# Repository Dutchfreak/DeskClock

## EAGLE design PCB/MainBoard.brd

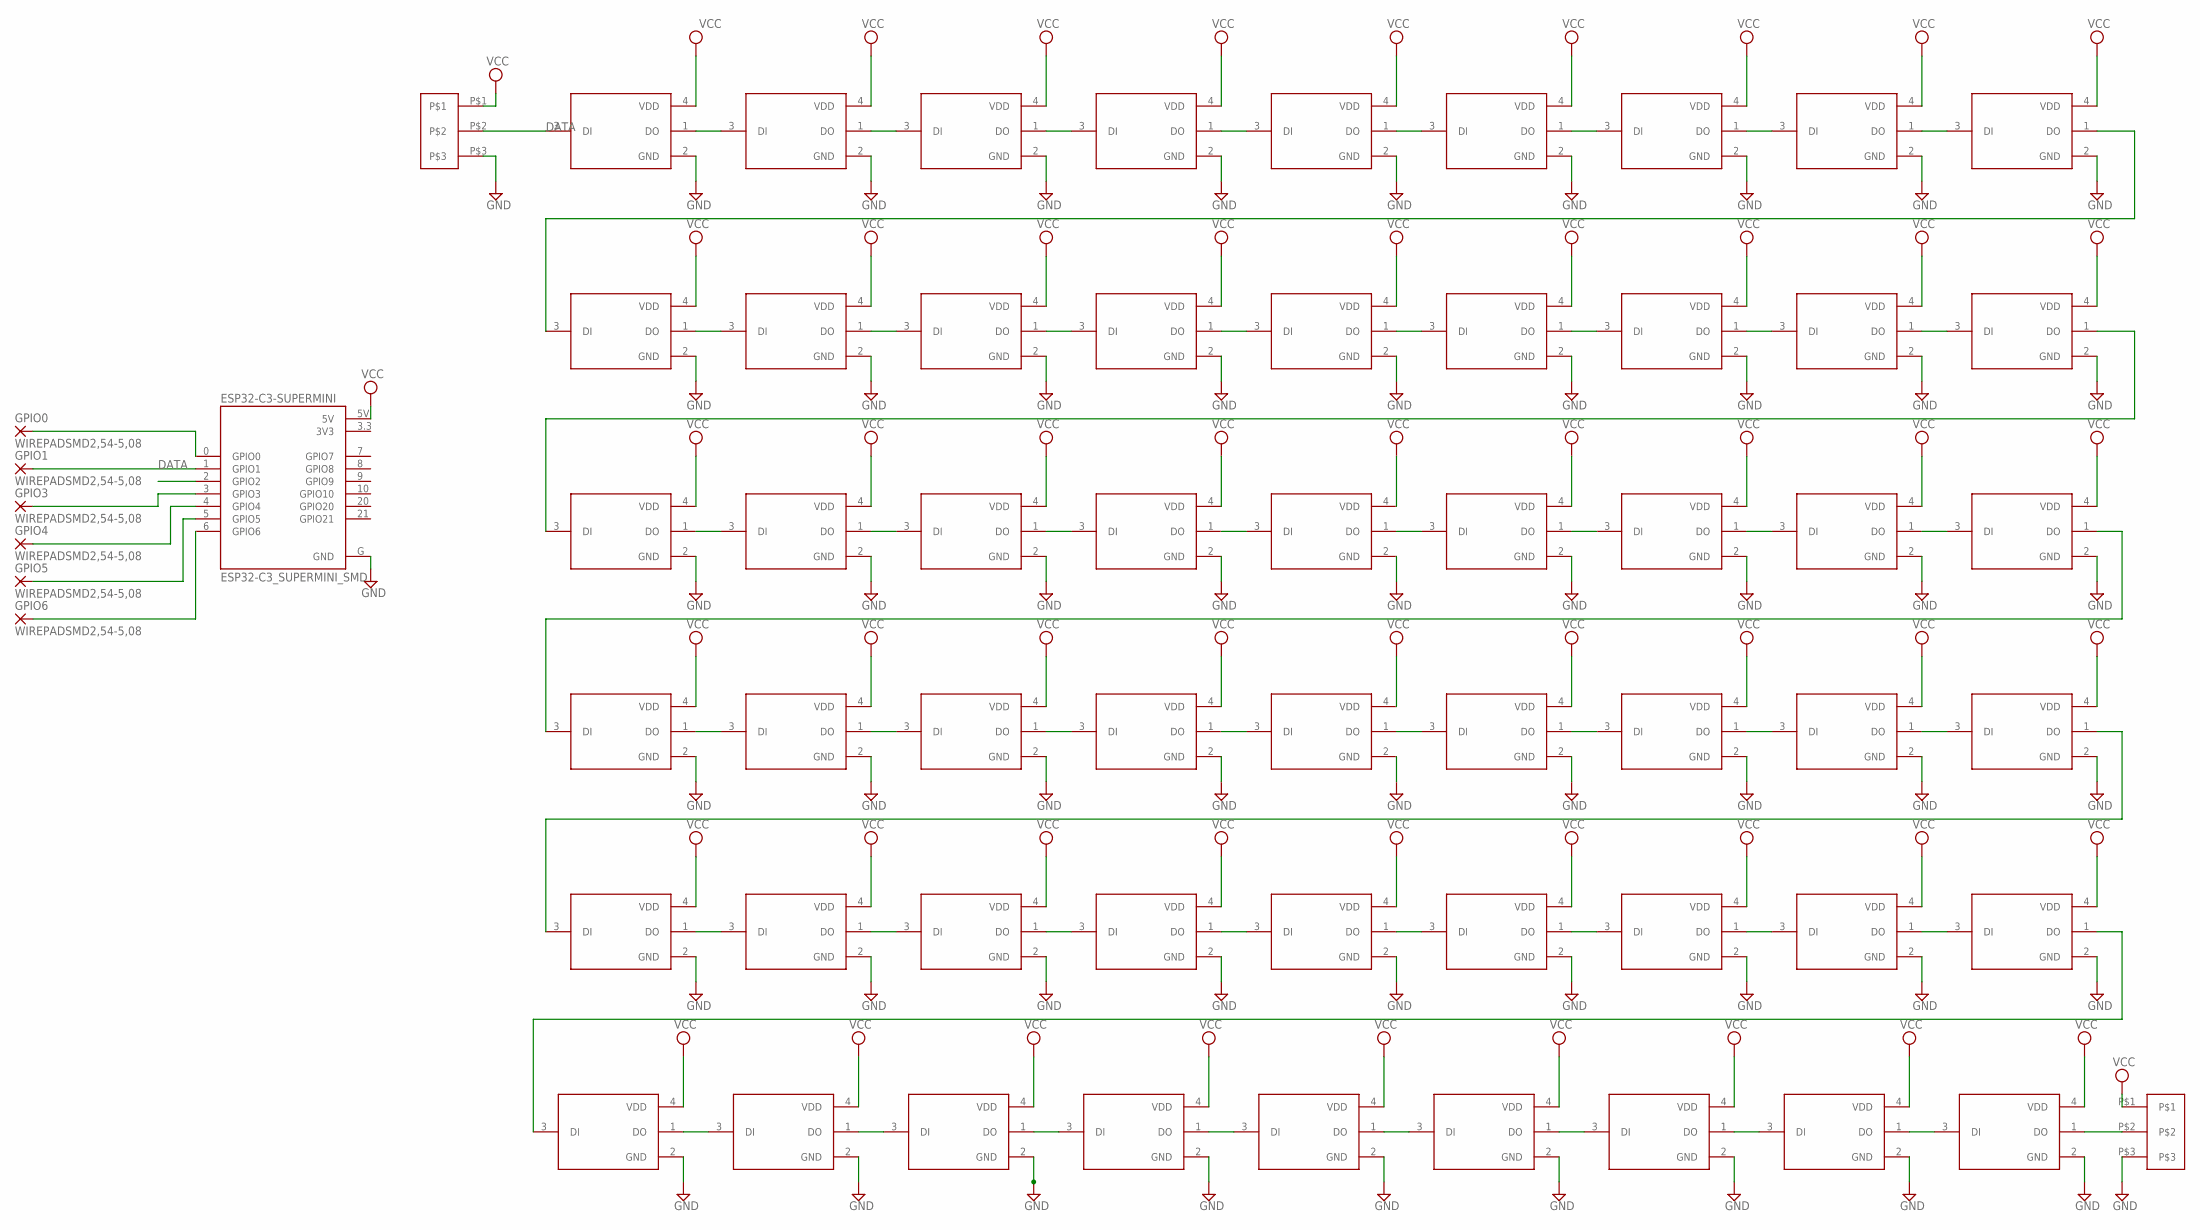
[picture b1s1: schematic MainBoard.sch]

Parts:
ESP32-C3-SUPERMINI: ESP32-C3_SUPERMINI_SMD; MODULE_ESP32-C3_SUPERMINI
GPIO0, GPIO1, GPIO3, GPIO4, GPIO5, GPIO6: WIREPADSMD2,54-5,08; SMD2,54-5,08
LED1, LED2, LED3, LED4, LED5, LED6, LED7, LED8, LED9, LED10, LED11, LED12, LED13, LED14, LED15, LED16, LED17, LED18, LED19, LED20, LED21, LED22, LED23, LED24, LED25, LED26, LED27, LED28, LED29, LED30, LED31, LED32, LED33, LED34, LED35, LED36, LED37, LED38, LED39, LED40, LED41, LED42, LED43, LED44, LED45, LED46, LED47, LED48, LED49, LED50, LED51, LED52, LED53, LED54: WS2812B2020; LED_WS2812B2020
U$1: POGO-3-M
U$2: POGO-3-F

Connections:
3V3: ESP32-C3-SUPERMINI.3.3 (3V3)
DATA: ESP32-C3-SUPERMINI.2 (GPIO2), LED1.3 (DI), U$2.P$2
GND: ESP32-C3-SUPERMINI.G (GND), LED1.2 (GND), LED2.2 (GND), LED3.2 (GND), LED4.2 (GND), LED5.2 (GND), LED6.2 (GND), LED7.2 (GND), LED8.2 (GND), LED9.2 (GND), LED10.2 (GND), LED11.2 (GND), LED12.2 (GND), LED13.2 (GND), LED14.2 (GND), LED15.2 (GND), LED16.2 (GND), LED17.2 (GND), LED18.2 (GND), LED19.2 (GND), LED20.2 (GND), LED21.2 (GND), LED22.2 (GND), LED23.2 (GND), LED24.2 (GND), LED25.2 (GND), LED26.2 (GND), LED27.2 (GND), LED28.2 (GND), LED29.2 (GND), LED30.2 (GND), LED31.2 (GND), LED32.2 (GND), LED33.2 (GND), LED34.2 (GND), LED35.2 (GND), LED36.2 (GND), LED37.2 (GND), LED38.2 (GND), LED39.2 (GND), LED40.2 (GND), LED41.2 (GND), LED42.2 (GND), LED43.2 (GND), LED44.2 (GND), LED45.2 (GND), LED46.2 (GND), LED47.2 (GND), LED48.2 (GND), LED49.2 (GND), LED50.2 (GND), LED51.2 (GND), LED52.2 (GND), LED53.2 (GND), LED54.2 (GND), U$1.P$3, U$2.P$3
unnamed: LED1.1 (DO), LED2.3 (DI)
unnamed: LED2.1 (DO), LED3.3 (DI)
unnamed: LED3.1 (DO), LED4.3 (DI)
unnamed: LED4.1 (DO), LED5.3 (DI)
unnamed: LED5.1 (DO), LED6.3 (DI)
unnamed: LED6.1 (DO), LED7.3 (DI)
unnamed: LED7.1 (DO), LED8.3 (DI)
unnamed: LED8.1 (DO), LED9.3 (DI)
unnamed: LED9.1 (DO), LED10.3 (DI)
unnamed: LED10.1 (DO), LED11.3 (DI)
unnamed: LED11.1 (DO), LED12.3 (DI)
unnamed: LED12.1 (DO), LED13.3 (DI)
unnamed: LED13.1 (DO), LED14.3 (DI)
unnamed: LED14.1 (DO), LED15.3 (DI)
unnamed: LED15.1 (DO), LED16.3 (DI)
unnamed: LED16.1 (DO), LED17.3 (DI)
unnamed: LED17.1 (DO), LED18.3 (DI)
unnamed: LED18.1 (DO), LED19.3 (DI)
unnamed: LED19.1 (DO), LED20.3 (DI)
unnamed: LED20.1 (DO), LED21.3 (DI)
unnamed: LED21.1 (DO), LED22.3 (DI)
unnamed: LED22.1 (DO), LED23.3 (DI)
unnamed: LED23.1 (DO), LED24.3 (DI)
unnamed: LED24.1 (DO), LED25.3 (DI)
unnamed: LED25.1 (DO), LED26.3 (DI)
unnamed: LED26.1 (DO), LED27.3 (DI)
unnamed: LED27.1 (DO), LED28.3 (DI)
unnamed: LED28.1 (DO), LED29.3 (DI)
unnamed: LED29.1 (DO), LED30.3 (DI)
unnamed: LED30.1 (DO), LED31.3 (DI)
unnamed: LED31.1 (DO), LED32.3 (DI)
unnamed: LED32.1 (DO), LED33.3 (DI)
unnamed: LED33.1 (DO), LED34.3 (DI)
unnamed: LED34.1 (DO), LED35.3 (DI)
unnamed: LED35.1 (DO), LED36.3 (DI)
unnamed: LED36.1 (DO), LED37.3 (DI)
unnamed: LED37.1 (DO), LED38.3 (DI)
unnamed: LED38.1 (DO), LED39.3 (DI)
unnamed: LED39.1 (DO), LED40.3 (DI)
unnamed: LED40.1 (DO), LED41.3 (DI)
unnamed: LED41.1 (DO), LED42.3 (DI)
unnamed: LED42.1 (DO), LED43.3 (DI)
unnamed: LED43.1 (DO), LED44.3 (DI)
unnamed: LED44.1 (DO), LED45.3 (DI)
unnamed: LED45.1 (DO), LED46.3 (DI)
unnamed: LED46.1 (DO), LED47.3 (DI)
unnamed: LED47.1 (DO), LED48.3 (DI)
unnamed: LED48.1 (DO), LED49.3 (DI)
unnamed: LED49.1 (DO), LED50.3 (DI)
unnamed: LED50.1 (DO), LED51.3 (DI)
unnamed: LED51.1 (DO), LED52.3 (DI)
unnamed: LED52.1 (DO), LED53.3 (DI)
unnamed: LED53.1 (DO), LED54.3 (DI)
unnamed: LED54.1 (DO), U$1.P$2
unnamed: ESP32-C3-SUPERMINI.0 (GPIO0), GPIO0.1
unnamed: ESP32-C3-SUPERMINI.1 (GPIO1), GPIO1.1
unnamed: ESP32-C3-SUPERMINI.6 (GPIO6), GPIO6.1
unnamed: ESP32-C3-SUPERMINI.5 (GPIO5), GPIO5.1
unnamed: ESP32-C3-SUPERMINI.4 (GPIO4), GPIO4.1
unnamed: ESP32-C3-SUPERMINI.3 (GPIO3), GPIO3.1
VCC: ESP32-C3-SUPERMINI.5V, LED1.4 (VDD), LED2.4 (VDD), LED3.4 (VDD), LED4.4 (VDD), LED5.4 (VDD), LED6.4 (VDD), LED7.4 (VDD), LED8.4 (VDD), LED9.4 (VDD), LED10.4 (VDD), LED11.4 (VDD), LED12.4 (VDD), LED13.4 (VDD), LED14.4 (VDD), LED15.4 (VDD), LED16.4 (VDD), LED17.4 (VDD), LED18.4 (VDD), LED19.4 (VDD), LED20.4 (VDD), LED21.4 (VDD), LED22.4 (VDD), LED23.4 (VDD), LED24.4 (VDD), LED25.4 (VDD), LED26.4 (VDD), LED27.4 (VDD), LED28.4 (VDD), LED29.4 (VDD), LED30.4 (VDD), LED31.4 (VDD), LED32.4 (VDD), LED33.4 (VDD), LED34.4 (VDD), LED35.4 (VDD), LED36.4 (VDD), LED37.4 (VDD), LED38.4 (VDD), LED39.4 (VDD), LED40.4 (VDD), LED41.4 (VDD), LED42.4 (VDD), LED43.4 (VDD), LED44.4 (VDD), LED45.4 (VDD), LED46.4 (VDD), LED47.4 (VDD), LED48.4 (VDD), LED49.4 (VDD), LED50.4 (VDD), LED51.4 (VDD), LED52.4 (VDD), LED53.4 (VDD), LED54.4 (VDD), U$1.P$1, U$2.P$1

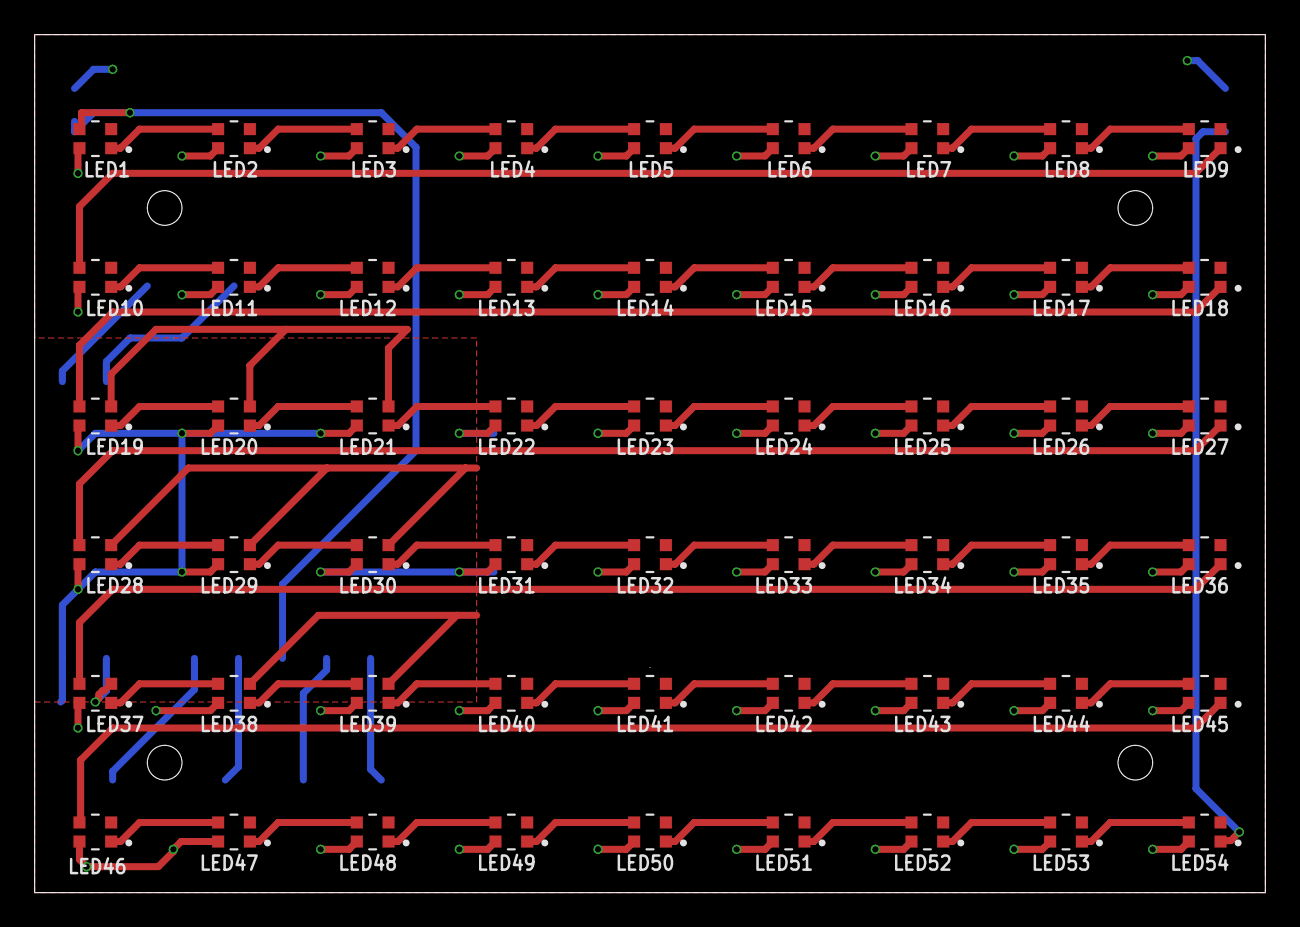
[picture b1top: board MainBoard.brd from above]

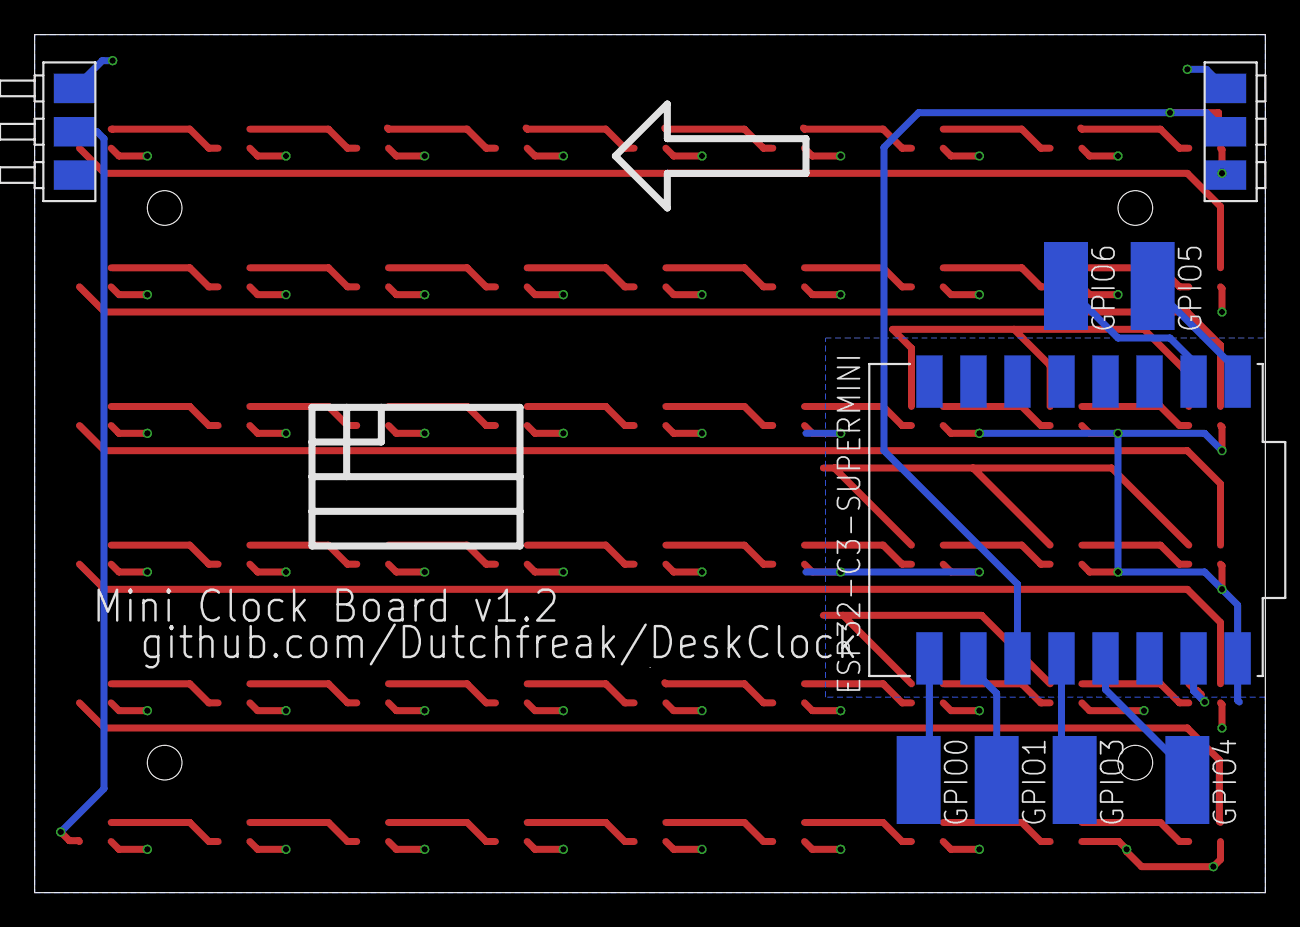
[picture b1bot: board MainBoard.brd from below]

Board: 2 copper layers, 71.0 x 49.5 mm, 63 parts (9 on the bottom side), 63 nets.

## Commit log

2025-08-31 Inital commit
2025-08-31 Diffuser Files
2025-09-01 Made entire Clock a bit bigger to fit screw heads
